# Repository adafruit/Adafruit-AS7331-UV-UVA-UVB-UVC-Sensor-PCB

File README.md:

## Adafruit AS7331 UV / UVA / UVB / UVC Sensor Breakout - STEMMA QT / Qwiic PCB

<a href="http://www.adafruit.com/products/6476"><br/>
Click here to purchase one from the Adafruit shop</a>

PCB files for the Adafruit AS7331 UV / UVA / UVB / UVC Sensor Breakout - STEMMA QT / Qwiic. 

Format is EagleCAD schematic and board layout
* https://www.adafruit.com/product/6476

### Description

The <b>Adafruit AS7331 UVA / UVB / UVC Sensor Breakout</b> is a perfect solution to UV sensing, no matter what 'type' you're sensing. Most UV sensors do just UVA, maybe ambient light too. But the AS7331 can read and differentiate between all the three bands. That means you can use it for human and agricultural UV alerts that tend to focus on  UVA and UVB as well as agricultural, germicidal, curing, and other UVC use cases. We particularly like that the three measurements are separated not just mixed together into one number.

The AS7331 has many gain and conversion settings configurable over I2C which means you can measure up to 349 mW/cm² on UVA channel, 386 mW/cm² on UVB and 169 mW/cm² on UVC at 1x gain, and with a responsivity as low as 2.38 nW/cm² per LSB.

In addition to the basic I2C connection, there's also the ability to change the default I2C address from 0x74 using the two jumpers on the back so you can have up to four sensors on the same bus. We also break out the READY pin that will let you know when a sensor conversion is complete, and the SYNC input, which can be used to synchronize the readings with an external pulse.

To make it easy to use, we mounted the tiny sensor on a STEMMA QT form factor breakout board, complete with level shifting circuitry and [SparkFun Qwiic](https://www.sparkfun.com/qwiic) compatible [Stemma QT](https://learn.adafruit.com/introducing-adafruit-stemma-qt) connectors. This means that you can, without needing to solder, connect our AS7331 breakout into your 3.3V or 5V microcontroller of choice be it an Arduino Uno, Raspberry Pi, or one of the many [CircuitPython-compatible boards](https://circuitpython.org/downloads).

Our Arduino and CircuitPython libraries make it easy to configure the AS7331 over I2C, with many included example sketches to help get you started. [QT Cable is not included, but we have a variety in the shop.](https://www.adafruit.com/?q=stemma+qt+cable&sort=BestMatch)

### License

Adafruit invests time and resources providing this open source design, please support Adafruit and open-source hardware by purchasing products from [Adafruit](https://www.adafruit.com)!

Designed by Limor Fried/Ladyada for Adafruit Industries.

Creative Commons Attribution/Share-Alike, all text above must be included in any redistribution. 
See license.txt for additional details.

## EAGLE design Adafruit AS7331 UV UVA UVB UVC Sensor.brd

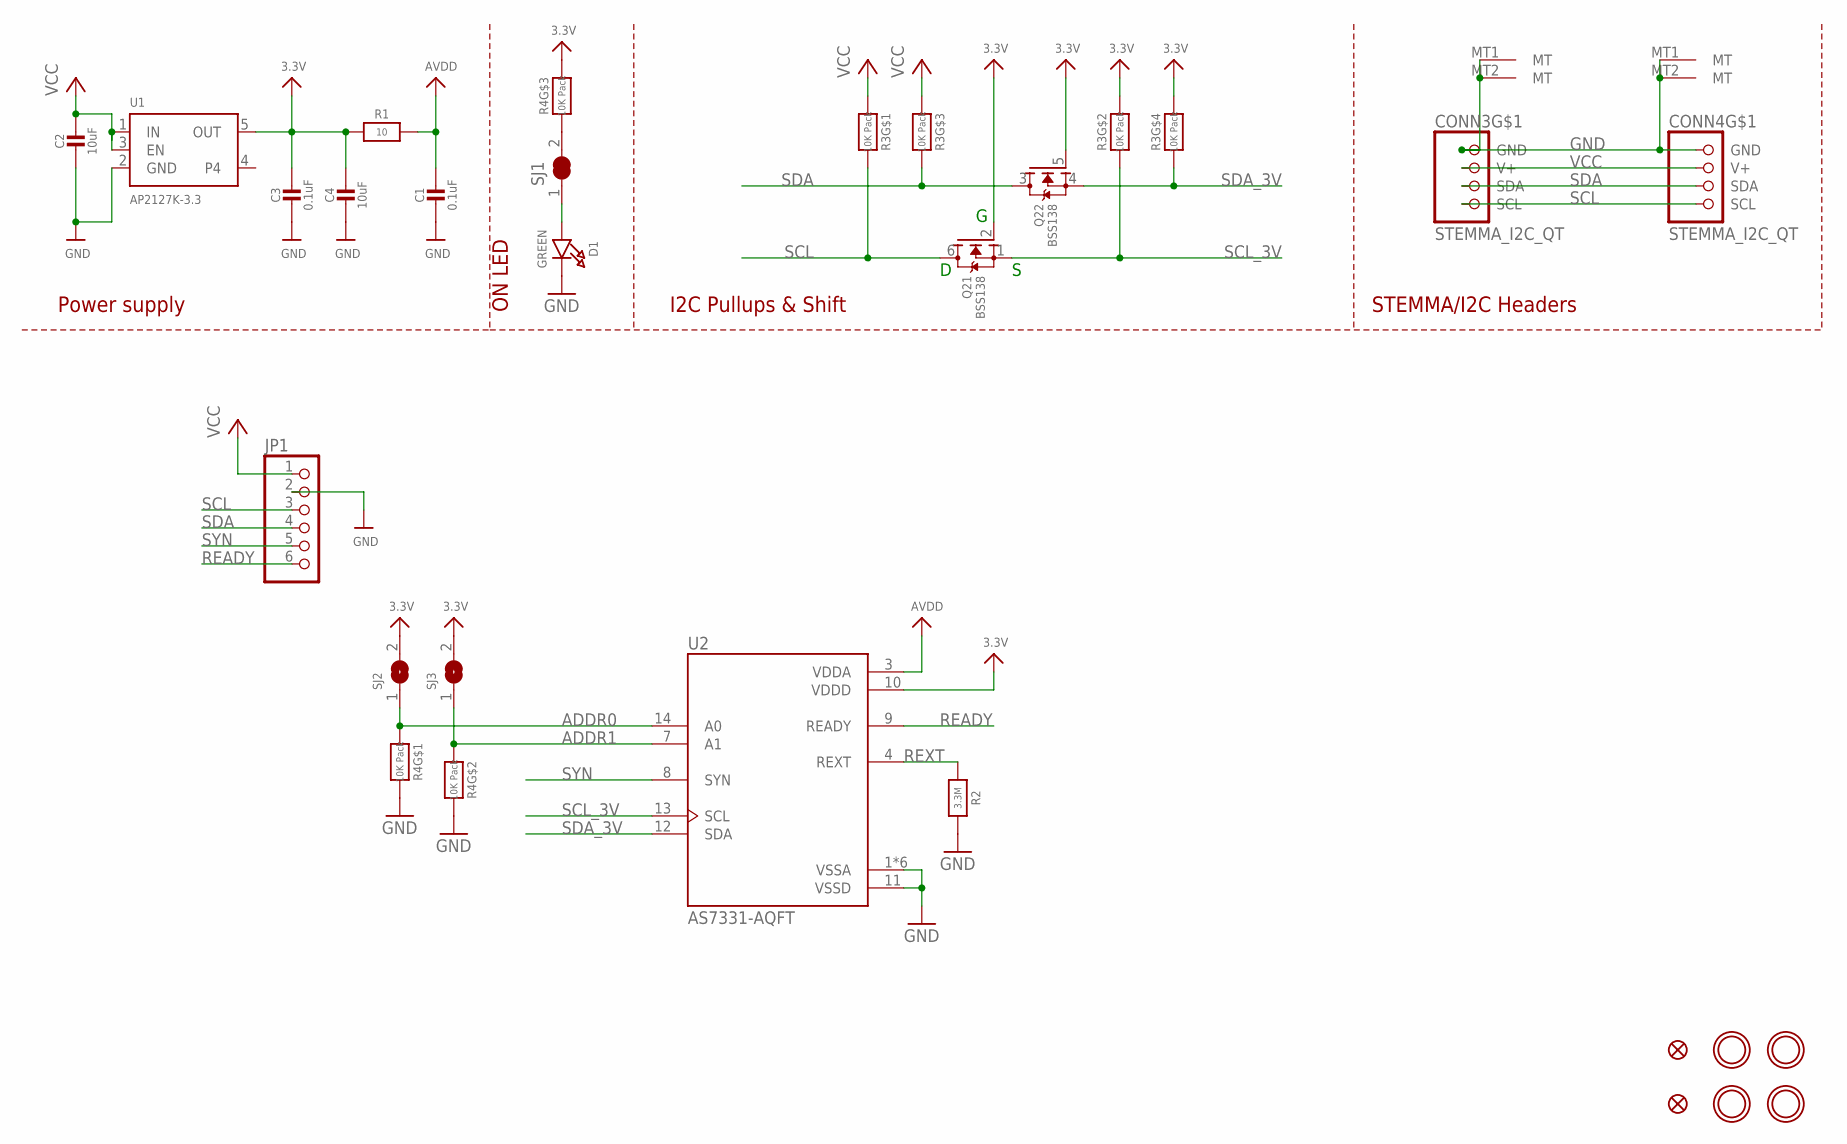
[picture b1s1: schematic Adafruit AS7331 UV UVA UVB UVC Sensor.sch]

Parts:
C1, C3: 0.1uF; 0603-NO
C2, C4: 10uF; 0805-NO
CONN3, CONN4: STEMMA_I2C_QT; JST_SH4
D1: GREEN; CHIPLED_0603_NOOUTLINE
FID3, FID4: FIDUCIAL_0.5MM
JP1: HEADER-1X670MIL; 1X06_ROUND_70
Q2: BSS138; SOT363
R1: 10; 0603-NO
R2: 3.3M; 0603-NO
R3, R4: 10K Pack; RESPACK_4X0603
SJ1: SOLDERJUMPER_CLOSED; SOLDERJUMPER_CLOSEDWIRE
SJ2, SJ3: SOLDERJUMPER; SOLDERJUMPER_ARROW_NOPASTE
U1: AP2127K-3.3; SOT23-5
U2: AS7331-AQFT; AS7331_SNAP
U$1, U$17, U$19, U$21: MOUNTINGHOLE2.5; MOUNTINGHOLE_2.5_PLATED

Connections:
3.3V: C3.1, C4.1, Q2.2 (G), Q2.5 (G), R1.1, R3.2 (1), R3.4 (1), R4.6 (2), SJ2.2, SJ3.2, U1.5 (OUT), U2.10 (VDDD)
ADDR0: R4.1, SJ2.1, U2.14 (A0)
ADDR1: R4.2 (1), SJ3.1, U2.7 (A1)
AVDD: C1.1, R1.2, U2.3 (VDDA)
GND: C1.2, C2.2, C3.2, C4.2, CONN3.1 (GND), CONN3.MT1 (MT), CONN3.MT2 (MT), CONN4.1 (GND), CONN4.MT1 (MT), CONN4.MT2 (MT), D1.C, JP1.2, R2.2, R4.7 (2), R4.8 (2), U1.2 (GND), U2.1 (VSSA), U2.2 (VSSA), U2.5 (VSSA), U2.6 (VSSA), U2.11 (VSSD), U2.15 (VSSA), U2.16 (VSSA)
unnamed: D1.A, SJ1.1
unnamed: R4.3 (1), SJ1.2
READY: JP1.6, U2.9 (READY)
REXT: R2.1, U2.4 (REXT)
SCL: CONN3.4 (SCL), CONN4.4 (SCL), JP1.3, Q2.6 (D), R3.8 (2)
SCL_3V: Q2.1 (S), R3.7 (2), U2.13 (SCL)
SDA: CONN3.3 (SDA), CONN4.3 (SDA), JP1.4, Q2.3 (D), R3.6 (2)
SDA_3V: Q2.4 (S), R3.5 (2), U2.12 (SDA)
SYN: JP1.5, U2.8 (SYN)
VCC: C2.1, CONN3.2 (V+), CONN4.2 (V+), JP1.1, R3.1, R3.3 (1), U1.1 (IN), U1.3 (EN)

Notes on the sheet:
I2C Pullups & Shift
STEMMA/I2C Headers
ON LED
Power supply

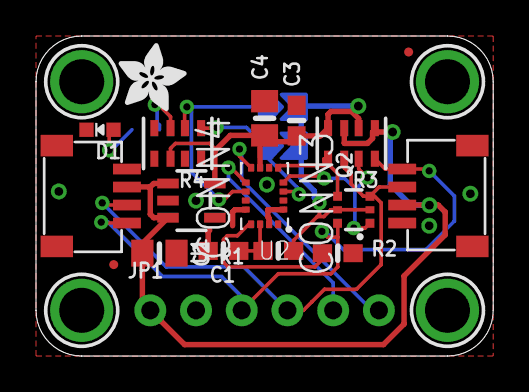
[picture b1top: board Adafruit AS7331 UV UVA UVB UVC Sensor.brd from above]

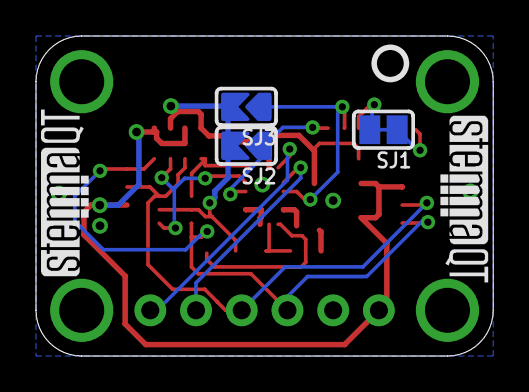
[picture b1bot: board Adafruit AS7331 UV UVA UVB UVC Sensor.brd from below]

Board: 2 copper layers, 25.4 x 17.8 mm, 45 parts (13 on the bottom side), 15 nets.

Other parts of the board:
PLABEL0: PLABEL0
PLABEL1: PLABEL1
PLABEL2: PLABEL2
PLABEL3: PLABEL3
PLABEL8: PLABEL8
PLABEL11: PLABEL11
PLABEL14: PLABEL14
PLABEL15: PLABEL15
PLABEL16: PLABEL16
PLABEL17: PLABEL17
PLABEL18: PLABEL18
PLABEL19: PLABEL19
PLABEL20: PLABEL20
PLABEL21: PLABEL21
PLABEL22: PLABEL22
PLABEL23: PLABEL23
PLABEL24: PLABEL24
U$22: ADAFRUIT_3.5MM
U$25: PCBFEAT-REV-040
U$30, U$31: STEMMAQT

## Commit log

2026-03-05 cookiecutter

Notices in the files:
parts and their libraries:
microbuilder: This work is placed in the public domain, and may be freely used for commercial and non-commercial work with the following conditions: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
